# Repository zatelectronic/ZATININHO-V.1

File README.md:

# ZATININHO-V.1
 ARDUINO STANDALONE

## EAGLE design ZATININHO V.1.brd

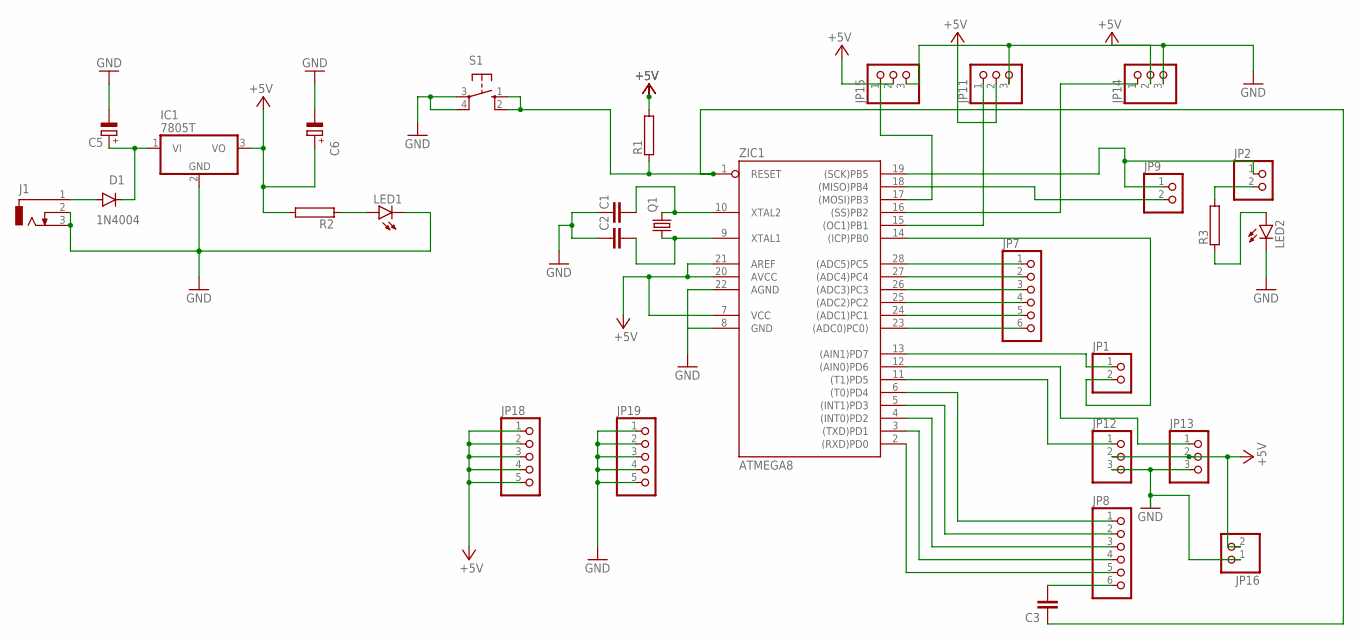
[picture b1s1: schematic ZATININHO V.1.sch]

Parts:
C1, C2: C2.5/2; C2.5-2
C3: C2,5-3; C2.5-3
C5, C6: CPOL-EUE2,5-6E; E2,5-6E
D1: 1N4004; DO41-10
IC1: 7805T; TO220H
J1: DCJ0303
JP1, JP2, JP9, JP16: PINHD-1X2; 1X02
JP7, JP8: PINHD-1X6; 1X06
JP11, JP12, JP13, JP14, JP15: PINHD-1X3; 1X03
JP18, JP19: PINHD-1X5; 1X05
LED1, LED2: LED5MM
Q1: CRYSTALHC49U-V; HC49U-V
R1, R2, R3: RRS1/4; RS1/4
S1: 10-XX; B3F-10XX
ZIC1: ATMEGA8; DIL28-3

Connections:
+5V: C6.+, IC1.3 (VO), JP11.2, JP12.2, JP13.2, JP14.2, JP15.2, JP16.2, JP18.1, JP18.2, JP18.3, JP18.4, JP18.5, R1.2, R2.2, ZIC1.7 (VCC), ZIC1.20 (AVCC), ZIC1.21 (AREF)
GND: C1.1, C2.1, C5.-, C6.-, IC1.2 (GND), J1.2, J1.3, JP11.3, JP12.3, JP13.3, JP14.3, JP15.3, JP16.1, JP19.1, JP19.2, JP19.3, JP19.4, JP19.5, LED1.K (C), LED2.K (C), S1.3, S1.4 (P1), ZIC1.8 (GND), ZIC1.22 (AGND)
unnamed: JP7.1, ZIC1.28 ((ADC5)PC5)
unnamed: JP7.2, ZIC1.27 ((ADC4)PC4)
unnamed: JP7.3, ZIC1.26 ((ADC3)PC3)
unnamed: JP7.4, ZIC1.25 ((ADC2)PC2)
unnamed: JP7.5, ZIC1.24 ((ADC1)PC1)
unnamed: JP7.6, ZIC1.23 ((ADC0)PC0))
unnamed: JP1.1, ZIC1.13 ((AIN1)PD7)
unnamed: JP2.1, JP9.1, ZIC1.19 ((SCK)PB5)
unnamed: JP12.1, ZIC1.11 ((T1)PD5)
unnamed: C3.1, R1.1, S1.1 (S), S1.2 (S1), ZIC1.1 (RESET)
unnamed: JP9.2, ZIC1.18 ((MISO)PB4)
unnamed: JP13.1, ZIC1.12 ((AIN0)PD6)
unnamed: JP2.2, R3.2
unnamed: JP15.1, ZIC1.17 ((MOSI)PB3)
unnamed: JP14.1, ZIC1.16 ((SS)PB2)
unnamed: JP11.1, ZIC1.15 ((OC1)PB1)
unnamed: JP1.2, ZIC1.14 ((ICP)PB0)
unnamed: JP8.5, ZIC1.2 ((RXD)PD0)
unnamed: JP8.4, ZIC1.3 ((TXD)PD1)
unnamed: JP8.3, ZIC1.4 ((INT0)PD2)
unnamed: JP8.2, ZIC1.5 ((INT1)PD3)
unnamed: JP8.1, ZIC1.6 ((T0)PD4)
unnamed: LED2.A, R3.1
unnamed: C3.2, JP8.6
unnamed: C2.2, Q1.1, ZIC1.9 (XTAL1)
unnamed: C1.2, Q1.2, ZIC1.10 (XTAL2)
unnamed: C5.+, D1.C, IC1.1 (VI)
unnamed: LED1.A, R2.1
unnamed: D1.A, J1.1

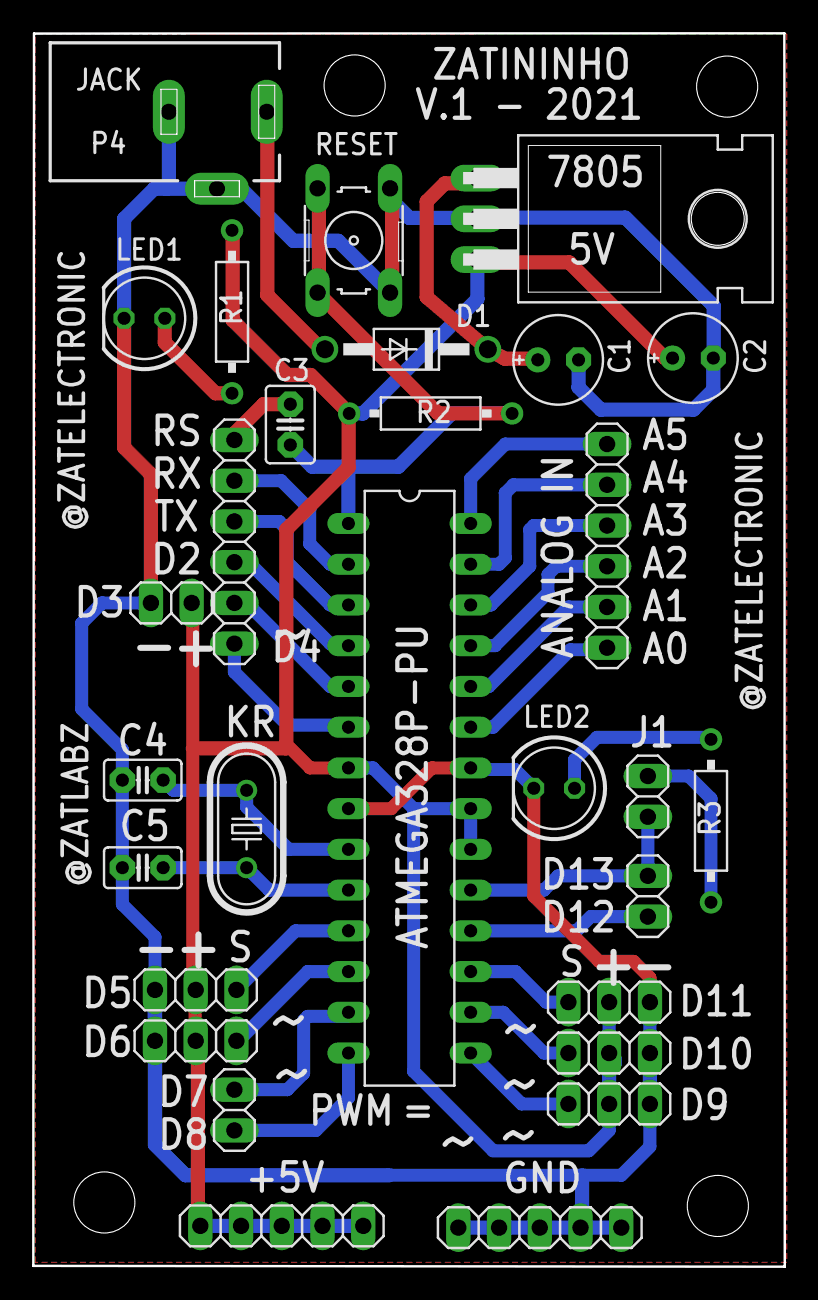
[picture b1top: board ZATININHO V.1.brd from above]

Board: 2 copper layers, 46.9 x 76.9 mm, 29 parts (0 on the bottom side), 31 nets.

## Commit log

2021-10-23 PRIMEIRO ENVIO
2021-10-25 ATUALIZAÇÃO
